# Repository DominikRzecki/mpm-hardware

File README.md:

# mpm-hardware
Mobile power measurement. Hardware repo
Update

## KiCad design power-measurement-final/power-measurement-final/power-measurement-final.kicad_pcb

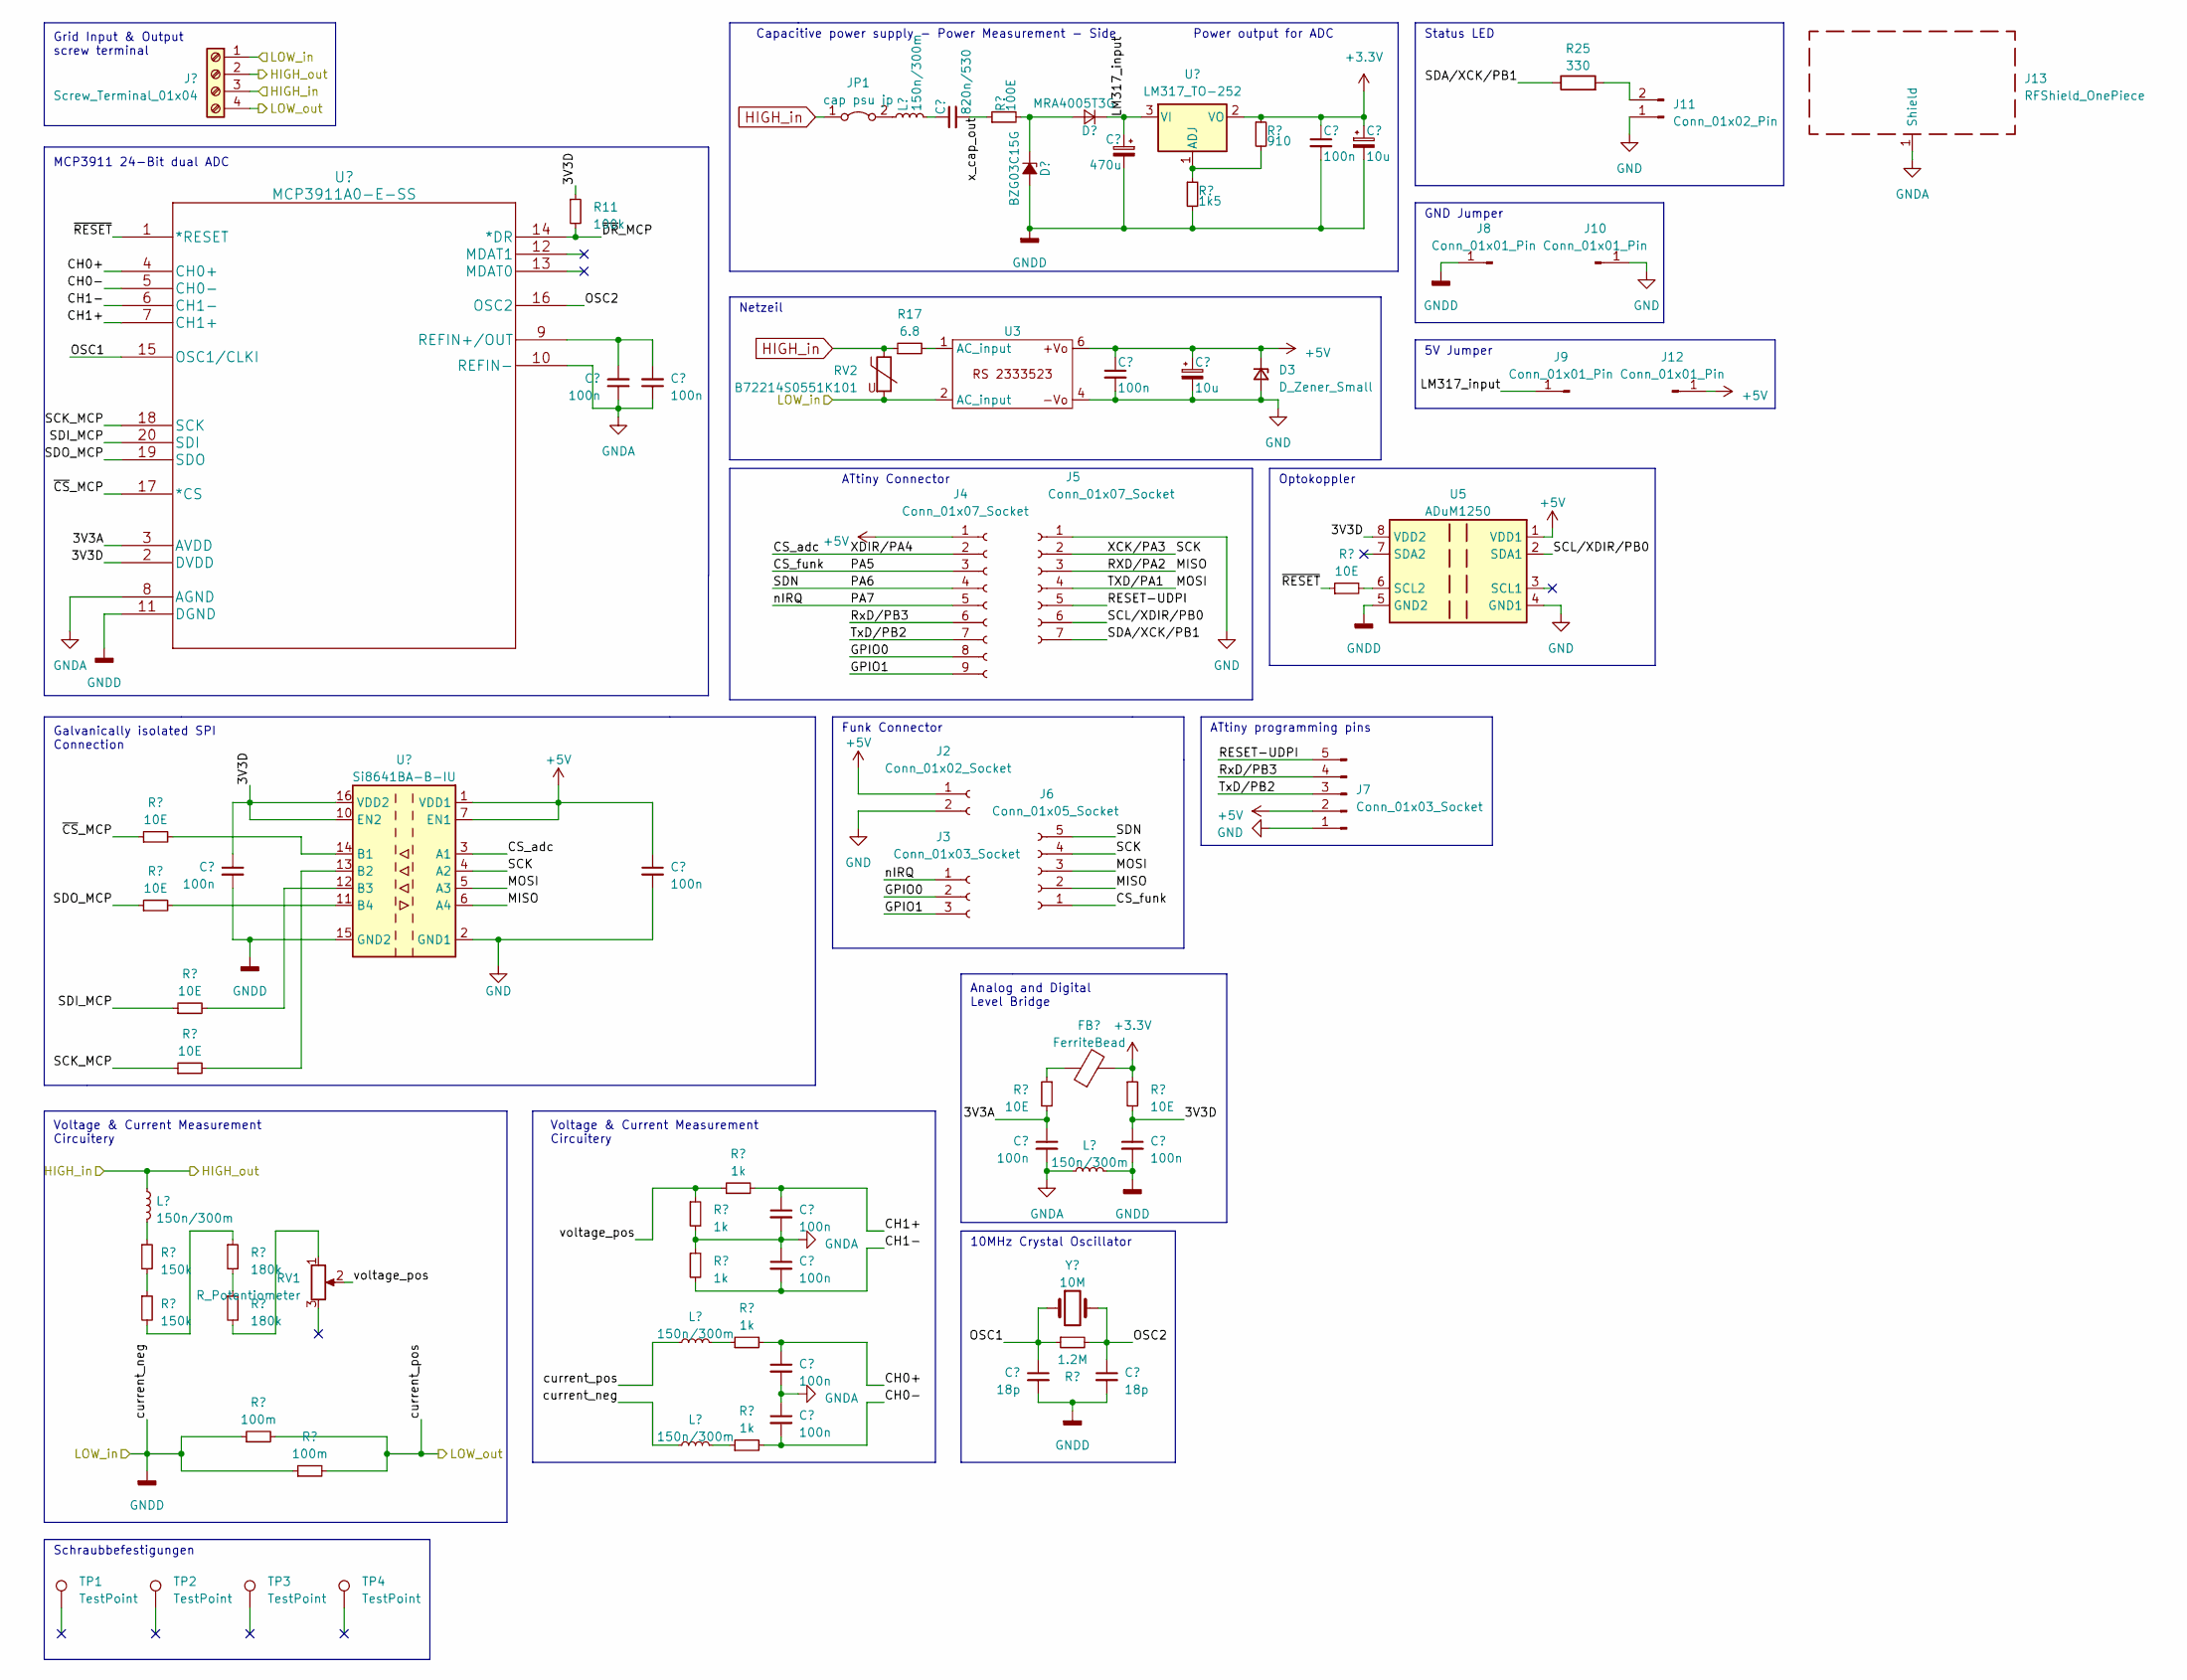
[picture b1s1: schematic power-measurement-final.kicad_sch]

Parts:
C1, C2, C3, C4, C5, C6, C7, C8, C11, C13, C15, C17: 100n; C_1206_3216Metric_Pad1.33x1.80mm_HandSolder
C9: 820n/530; C_Rect_L26.5mm_W10.5mm_P22.50mm_MKS4
C10, C12: 18p; C_0805_2012Metric_Pad1.18x1.45mm_HandSolder
C14: 470u; CP_Radial_D10.0mm_P5.00mm
C16, C18: 10u; C_1206_3216Metric_Pad1.33x1.80mm_HandSolder
D1: BZG03C15G; D_SMA-SMB_Universal_Handsoldering
D2: MRA4005T3G; D_MicroMELF_Handsoldering
D3: D_Zener_Small; D_1206_3216Metric_Pad1.42x1.75mm_HandSolder
FB1: FerriteBead; L_1210_3225Metric_Pad1.42x2.65mm_HandSolder
J1: Screw_Terminal_01x04; PhoenixContact_MSTBVA_2,5_4-G-5,08_1x04_P5.08mm_Vertical
J2: Conn_01x02_Socket; PinSocket_1x02_P2.54mm_Vertical
J3: Conn_01x03_Socket; PinSocket_1x03_P2.54mm_Vertical
J4: Conn_01x07_Socket; PinSocket_1x09_P2.54mm_Vertical
J5: Conn_01x07_Socket; PinSocket_1x07_P2.54mm_Vertical
J6: Conn_01x05_Socket; PinSocket_1x05_P2.54mm_Vertical
J7: Conn_01x03_Socket; PinHeader_1x05_P2.54mm_Vertical
J8, J9, J10, J12: Conn_01x01_Pin; PinHeader_1x01_P2.54mm_Vertical
J11: Conn_01x02_Pin; PinHeader_1x02_P2.54mm_Vertical
J13: RFShield_OnePiece; Laird_Technologies_BMI-S-209-F_29.36x18.50mm
JP1: cap psu jp; PinHeader_1x02_P2.54mm_Vertical
L1, L2, L3, L4, L5: 150n/300m; L_1206_3216Metric
R1, R2: 150k; R_1206_3216Metric_Pad1.30x1.75mm_HandSolder
R3, R4, R5, R6, R19, R21, R24: 10E; R_0805_2012Metric_Pad1.20x1.40mm_HandSolder
R7, R8: 180k; R_1206_3216Metric_Pad1.30x1.75mm_HandSolder
R9, R10: 100m; R_2512_6332Metric
R11: 100k; R_1206_3216Metric
R12, R13, R14, R15, R16: 1k; R_1206_3216Metric_Pad1.30x1.75mm_HandSolder
R17: 6.8; R_Radial_Power_L12.0mm_W8.0mm_P5.00mm
R18: 100E; R_1206_3216Metric_Pad1.30x1.75mm_HandSolder
R20: 1.2M; R_1206_3216Metric_Pad1.30x1.75mm_HandSolder
R22: 1k5; R_1206_3216Metric_Pad1.30x1.75mm_HandSolder
R23: 910; R_1206_3216Metric_Pad1.30x1.75mm_HandSolder
R25: 330; R_1206_3216Metric_Pad1.30x1.75mm_HandSolder
RV1: R_Potentiometer; Potentiometer_ACP_CA9-V10_Vertical_Hole
RV2: B72214S0551K101; R_Axial_DIN0204_L3.6mm_D1.6mm_P7.62mm_Horizontal
TP1, TP2, TP3, TP4: TestPoint; TestPoint_Plated_Hole_D3.0mm
U1: MCP3911A0-E-SS; SSOP-20_5.3x7.2mm_P0.65mm
U2: Si8641BA-B-IU; SOIC-16_3.9x9.9mm_P1.27mm
U3: RS_2333523
U4: LM317_TO-252; TO-252-2
U5: ADuM1250; SO-8_5.3x6.2mm_P1.27mm
Y1: 10M; Crystal_HC49-4H_Vertical

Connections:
+3.3V: C17.1, C18.1, FB1.2, R21.1, R23.1, U4.2 (VO)
+5V: C4.1, C13.1, C16.1, D3.1 (K), J2.1, J4.1, J7.2, J12.1, U2.1 (VDD1), U2.7 (EN1), U3.6, U5.1 (VDD1)
/3V3A: C11.1, R19.2, U1.3 (AVDD)
/3V3D: C1.1, C15.1, R11.1, R21.2, U1.2 (DVDD), U2.10 (EN2), U2.16 (VDD2), U5.8 (VDD2)
/CH0+: C7.1, R15.2, U1.4 (CH0+)
/CH0-: C8.2, R16.2, U1.5 (CH0-)
/CH1+: C5.1, R14.2, U1.7 (CH1+)
/CH1-: C6.2, R13.2, U1.6 (CH1-)
/CS_adc: J4.2, U2.3 (A1)
/CS_funk: J4.3, J6.1
/GPIO0: J3.2, J4.8
/GPIO1: J3.3, J4.9
/LM317_input: C14.1, D2.1 (K), J9.1, U4.3 (VI)
/MISO: J5.3, J6.2, U2.6 (A4)
/MOSI: J5.4, J6.3, U2.5 (A3)
/OSC1: C10.1, R20.1, U1.15 (OSC1/CLKI), Y1.1
/OSC2: C12.1, R20.2, U1.16 (OSC2), Y1.2
/PA6: J4.4, J6.5
/PA7: J3.1, J4.5
/RESET-UDPI: J5.5, J7.5
/RxD/PB3: J4.6, J7.4
/SCK: J5.2, J6.4, U2.4 (A2)
/SCK_MCP: R6.1, U1.18 (SCK)
/SCL/XDIR/PB0: J5.6, U5.2 (SDA1)
/SDA/XCK/PB1: J5.7, R25.1
/SDI_MCP: R5.1, U1.20 (SDI)
/SDO_MCP: R4.1, U1.19 (SDO)
/TxD/PB2: J4.7, J7.3
/current_pos: J1.4, L2.1, R9.2, R10.2
/voltage_pos: R12.1, R14.1, RV1.2
/x_cap_out: C9.2, R18.1
/~CS_MCP: R3.1, U1.17 (*CS)
/~DR_MCP: R11.2, U1.14 (*DR)
/~RESET: R24.1, U1.1 (*RESET)
GND: C4.2, C13.2, C16.2, D3.2 (A), J2.2, J5.1, J7.1, J10.1, J11.1, U2.2 (GND1), U2.8 (GND1), U3.4, U5.4 (GND1)
GNDA: C2.1, C3.1, C5.2, C6.1, C7.2, C8.1, C11.2, J13.1 (Shield), L5.1, R12.2, R13.1, U1.8 (AGND), U1.10 (REFIN-)
GNDD: C1.2, C10.2, C12.2, C14.2, C15.2, C17.2, C18.2, D1.2 (A), J1.1, J8.1, L3.1, L5.2, R9.1, R10.1, R22.2, RV2.2, U1.11 (DGND), U2.9 (GND2), U2.15 (GND2), U3.2 (AC_input), U5.5 (GND2)
HIGH_in: J1.2, J1.3, JP1.1 (A), L1.1, R17.1, RV2.1
unnamed: C9.1, L4.2
unnamed: D1.1 (K), D2.2 (A), R18.2
unnamed: FB1.1, R19.1
unnamed: J11.2, R25.2
unnamed: JP1.2 (B), L4.1
unnamed: L1.2, R1.1
unnamed: L2.2, R15.1
unnamed: L3.2, R16.1
unnamed: R1.2, R2.1
unnamed: R2.2, R7.1
unnamed: R7.2, R8.1
unnamed: R8.2, RV1.1
unnamed: R17.2, U3.1 (AC_input)
unnamed: C2.2, C3.2, U1.9 (REFIN+/OUT)
unnamed: R3.2, U2.14 (B1)
unnamed: R6.2, U2.13 (B2)
unnamed: R5.2, U2.12 (B3)
unnamed: R4.2, U2.11 (B4)
unnamed: R22.1, R23.2, U4.1 (ADJ)
unnamed: R24.2, U5.6 (SCL2)

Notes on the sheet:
Netzeil
Voltage & Current Measurement Circuitery
10MHz Crystal Oscillator
Funk Connector
Status LED
ATtiny Connector
Optokoppler
MCP3911 24-Bit dual ADC
5V Jumper
Capacitive power supply - Power Measurement - Side
Power output for ADC
ATtiny programming pins
Schraubbefestigungen
GND Jumper
Galvanically isolated SPI Connection
Grid Input & Output screw terminal
Analog and Digital Level Bridge

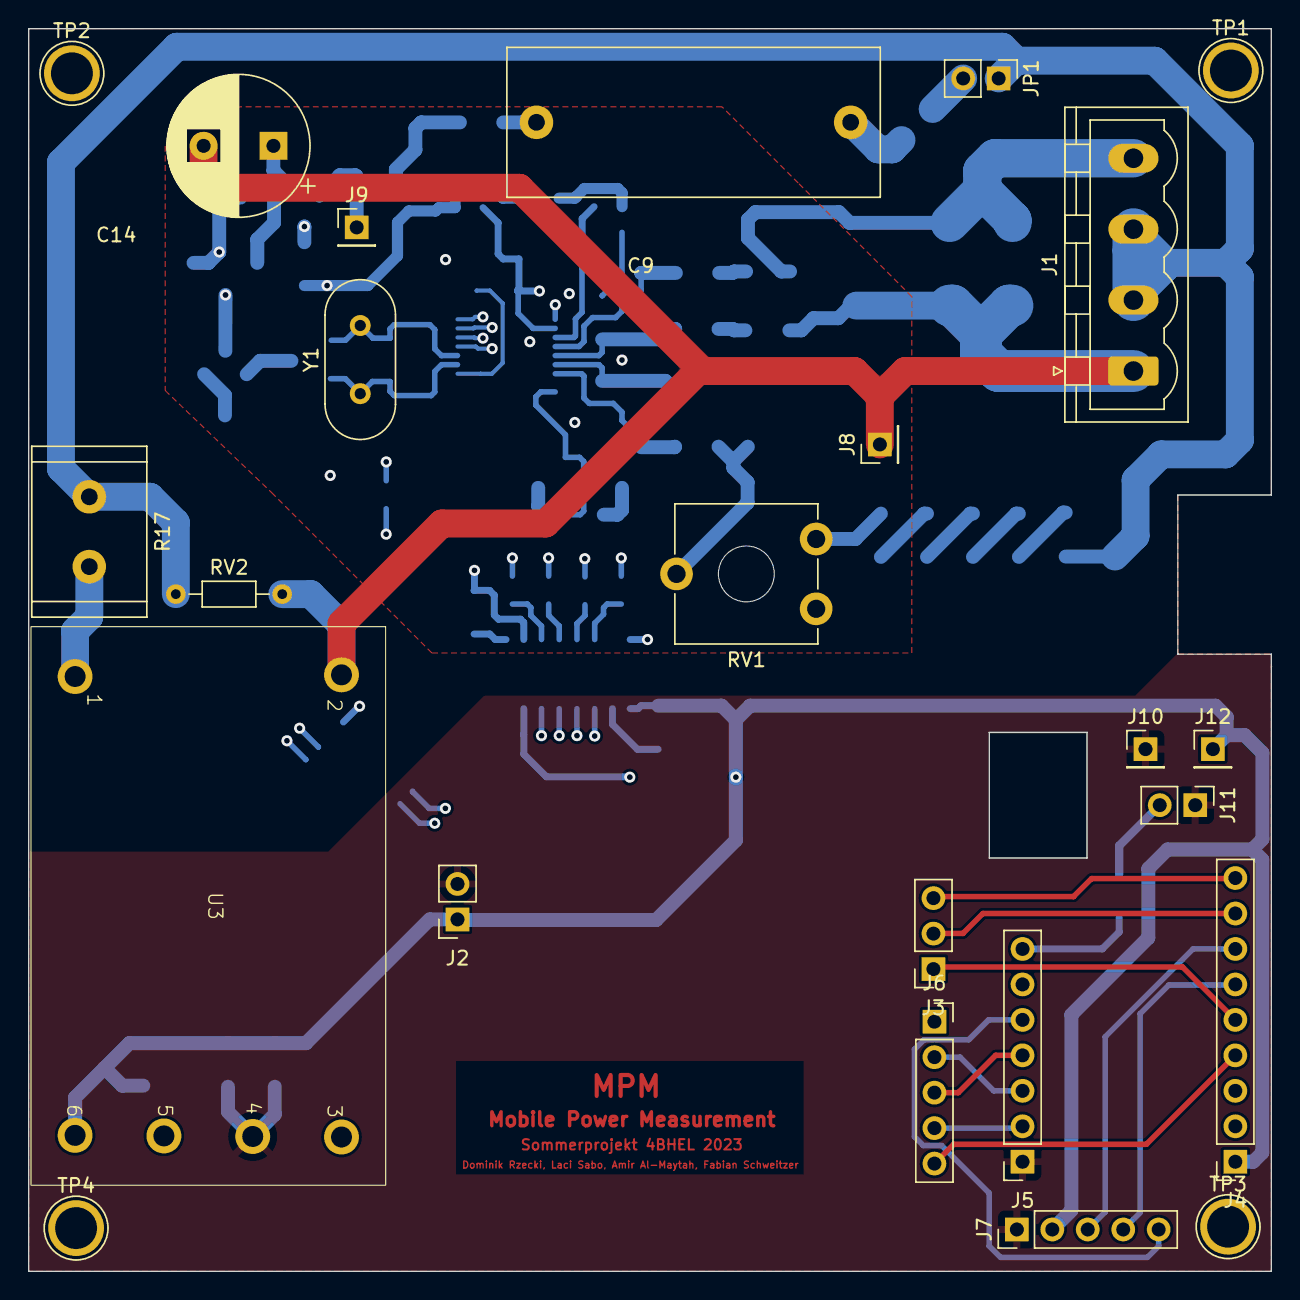
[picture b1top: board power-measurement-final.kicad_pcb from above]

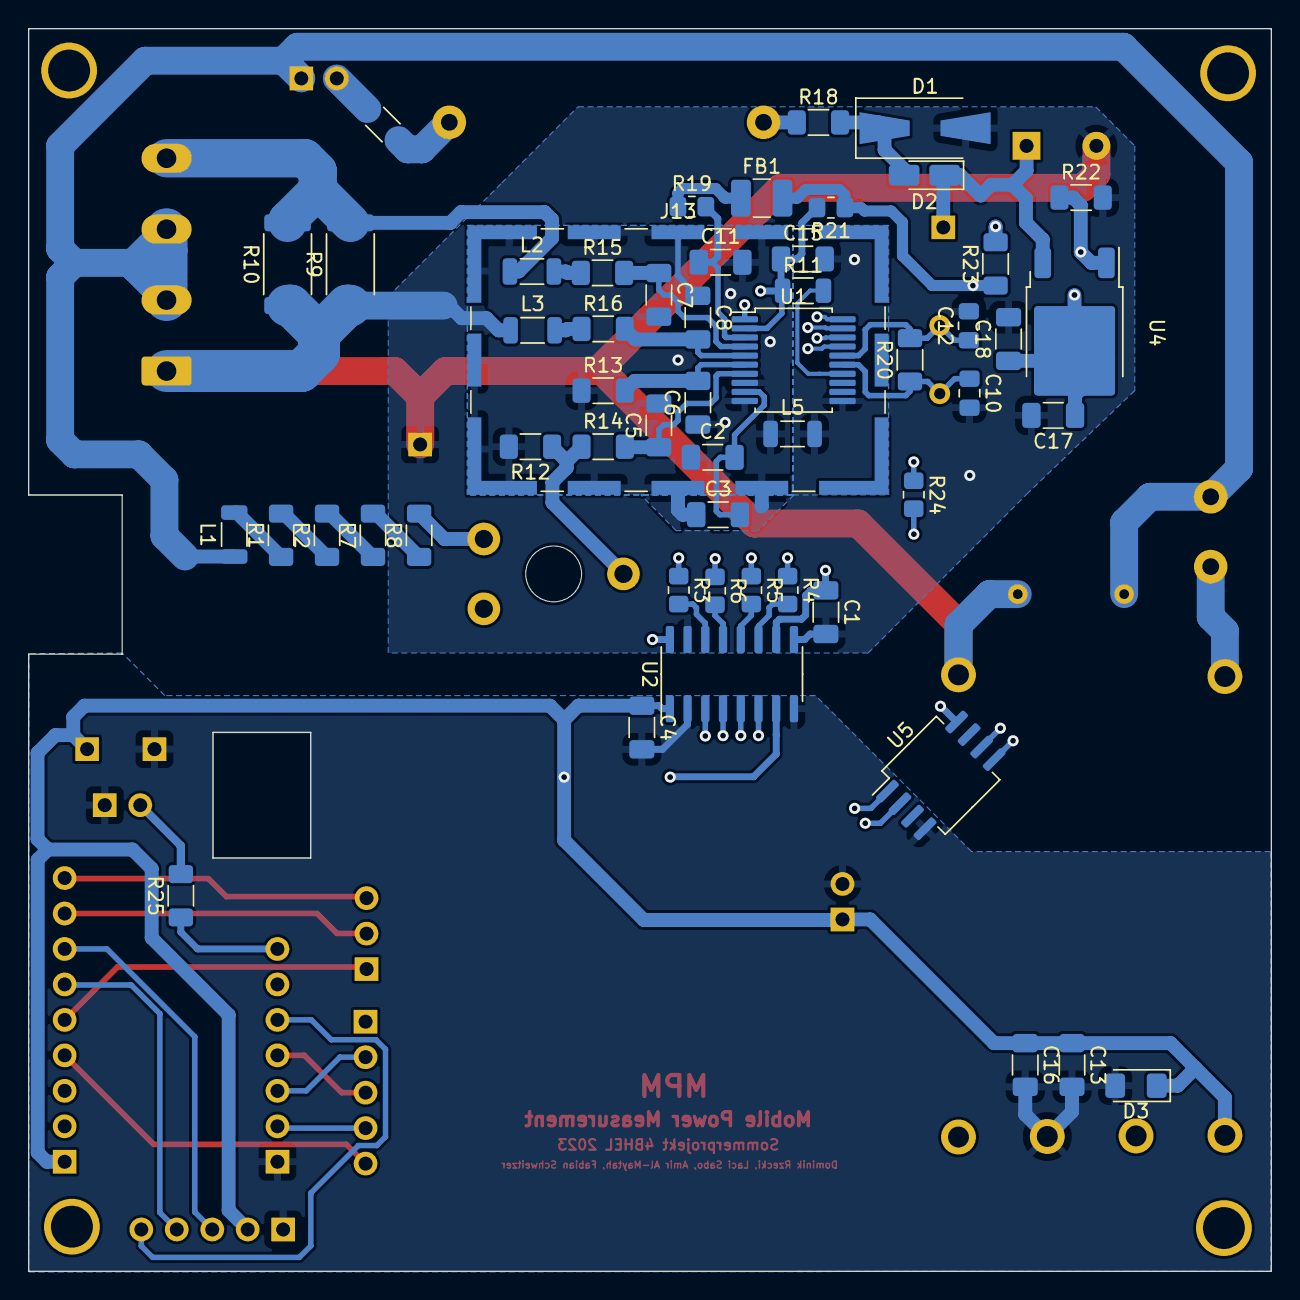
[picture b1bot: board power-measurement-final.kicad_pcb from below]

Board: 4 copper layers, 89.0 x 89.0 mm, 78 parts (54 on the bottom side), 58 nets.

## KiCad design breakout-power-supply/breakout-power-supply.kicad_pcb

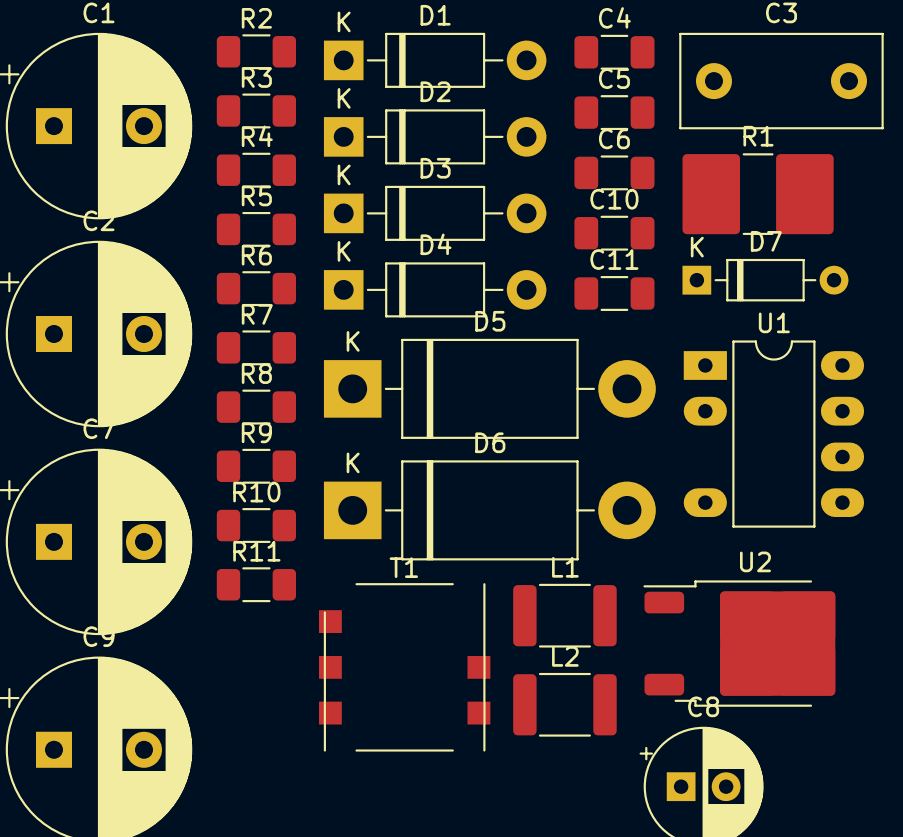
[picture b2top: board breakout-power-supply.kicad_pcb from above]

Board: 2 copper layers, 34 parts (0 on the bottom side), 20 nets, no tracks yet.

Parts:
C1, C2: 6u8; CP_Radial_D10.0mm_P5.00mm
C3: 1n; C_Disc_D11.0mm_W5.0mm_P7.50mm
C4, C5, C6: 1u; C_1206_3216Metric_Pad1.33x1.80mm_HandSolder
C7: 1000u; CP_Radial_D10.0mm_P5.00mm
C8: 470u; CP_Radial_D6.3mm_P2.50mm
C9: 470u; CP_Radial_D10.0mm_P5.00mm
C10: 100n; C_1206_3216Metric_Pad1.33x1.80mm_HandSolder
C11: 10u; C_1206_3216Metric_Pad1.33x1.80mm_HandSolder
D1, D2, D3, D4: 1N4007; D_DO-41_SOD81_P10.16mm_Horizontal
D5: D; D_DO-201AD_P15.24mm_Horizontal
D6: 1N5822; D_DO-201AD_P15.24mm_Horizontal
D7: 1N4148; D_DO-35_SOD27_P7.62mm_Horizontal
L1, L2: 1m; L_1812_4532Metric_Pad1.30x3.40mm_HandSolder
R1: 10E; R_2816_7142Metric_Pad3.20x4.45mm_HandSolder
R2: 270k; R_1206_3216Metric_Pad1.30x1.75mm_HandSolder
R3: 330E; R_1206_3216Metric_Pad1.30x1.75mm_HandSolder
R4, R8: 28.7k; R_1206_3216Metric_Pad1.30x1.75mm_HandSolder
R5: 4.42k; R_1206_3216Metric_Pad1.30x1.75mm_HandSolder
R6, R7: 12E; R_1206_3216Metric_Pad1.30x1.75mm_HandSolder
R9: 820E; R_1206_3216Metric_Pad1.30x1.75mm_HandSolder
R10: 1k5; R_1206_3216Metric_Pad1.30x1.75mm_HandSolder
R11: 910; R_1206_3216Metric_Pad1.30x1.75mm_HandSolder
T1: PA0510NL; Pulse_PA2002NL-PA2008NL-PA2009NL
U1: LNK625PG; PowerIntegrations_PDIP-8C
U2: LM317_TO-252; TO-252-2

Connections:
+3.3V: C10.1, C11.1, R11.1, U2.2 (VO)
/5V: C8.1, C9.1, L2.2, R9.2, U2.3 (VI)
/HIGH_in: D1.2 (A), D2.1 (K)
GND: C5.2, C7.2, C8.2, C9.2, C10.2, C11.2, D6.2 (A), R9.1, R10.2
unnamed: C2.2, C4.2, C6.2, L1.2, R5.1, T1.5, U1.5 (S), U1.6 (S), U1.7 (S), U1.8 (S)
unnamed: C3.2, R2.1, R3.2
unnamed: C5.1, R6.1
unnamed: C7.1, L2.1, T1.3
unnamed: C1.1, C2.1, C3.1, D1.1 (K), D3.1 (K), R2.2, T1.1
unnamed: C1.2, D2.2 (A), D4.2 (A), L1.1
unnamed: D3.2 (A), D4.1 (K), R1.2
unnamed: D5.2 (A), U1.4 (D)
unnamed: D5.1 (K), R3.1
unnamed: D6.1 (K), R6.2, T1.6
unnamed: D7.2 (A), R7.1
unnamed: C6.1, D7.1 (K), R8.2
unnamed: R4.2, R7.2, T1.4
unnamed: C4.1, R8.1, U1.2 (BP)
unnamed: R4.1, R5.2, U1.1 (FB)
unnamed: R10.1, R11.2, U2.1 (ADJ)

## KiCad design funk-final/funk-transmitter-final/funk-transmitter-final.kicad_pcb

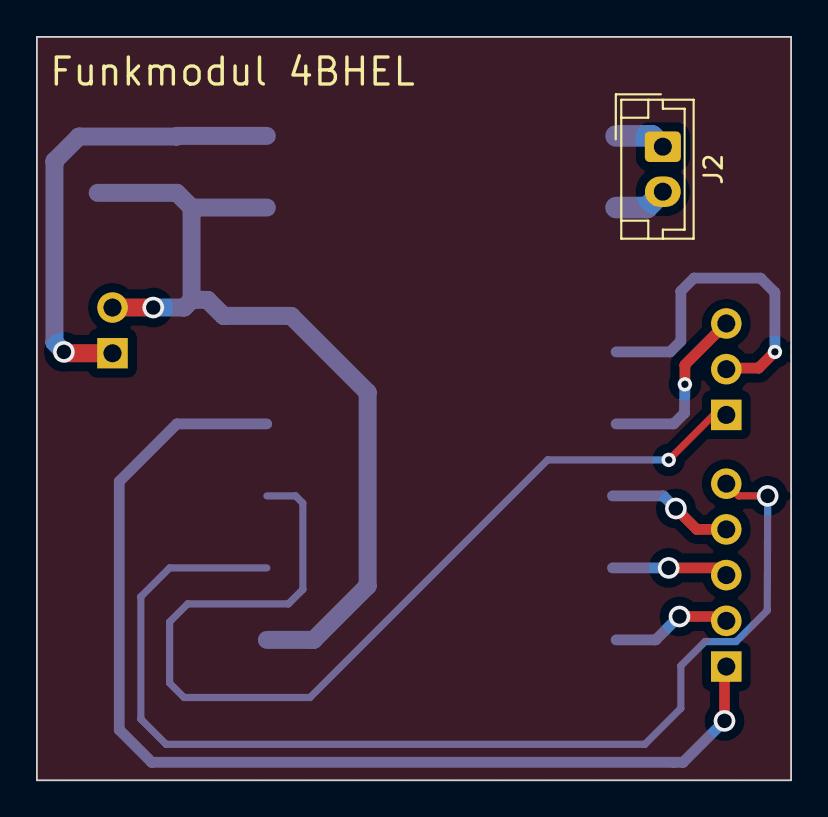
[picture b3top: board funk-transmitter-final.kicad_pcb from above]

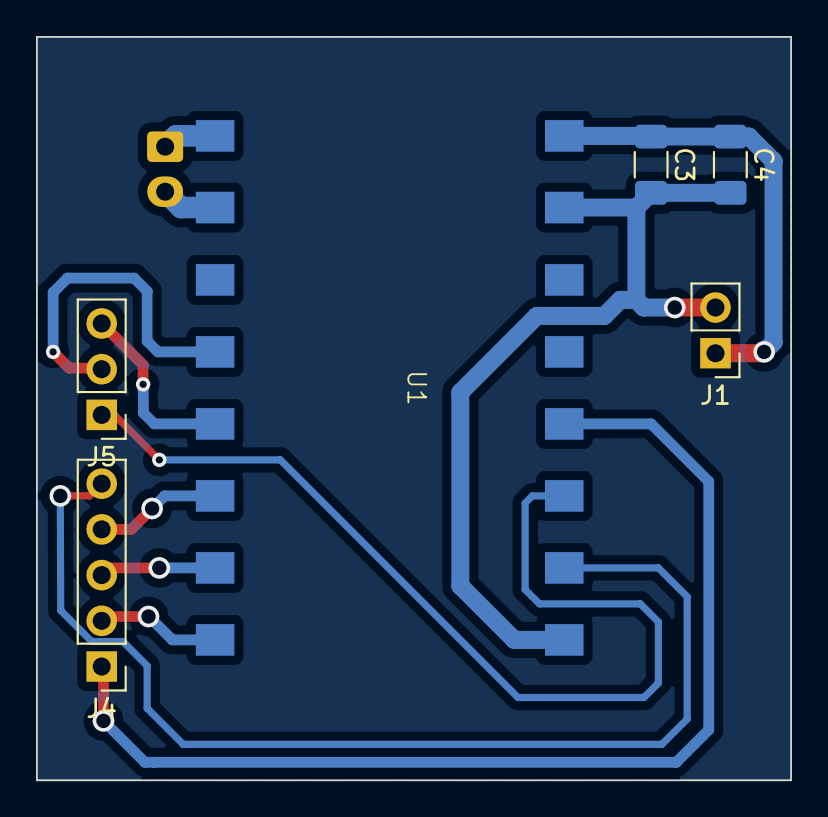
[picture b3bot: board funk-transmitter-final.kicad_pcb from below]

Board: 4 copper layers, 41.9 x 41.3 mm, 7 parts (6 on the bottom side), 9 nets.

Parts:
C3: 100n; C_1206_3216Metric_Pad1.33x1.80mm_HandSolder
C4: 47u; C_1206_3216Metric_Pad1.33x1.80mm_HandSolder
J1: Conn_01x02_Socket; PinHeader_1x02_P2.54mm_Vertical
J2: Conn_01x02_Socket; JST_EH_B2B-EH-A_1x02_P2.50mm_Vertical
J4: Conn_01x05_Socket; PinHeader_1x05_P2.54mm_Vertical
J5: Conn_01x03_Socket; PinHeader_1x03_P2.54mm_Vertical
U1: Si4463_eigen; Si4463

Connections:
/GPIO0: J5.2, U1.12 (GPIO0)
/GPIO1: J5.3, U1.13 (GPIO1)
/SCLK: J4.2, U1.16 (SCLK)
/SDI: J4.3, U1.15 (SDI)
/SDN: J4.1, U1.5 (SDN)
/SDO: J4.4, U1.14 (SDO)
/nIRQ: J5.1, U1.6 (nIRQ)
/nSEL: J4.5, U1.7 (nSEL)
GND: J1.2, U1.2 (GND), U1.8 (GND)

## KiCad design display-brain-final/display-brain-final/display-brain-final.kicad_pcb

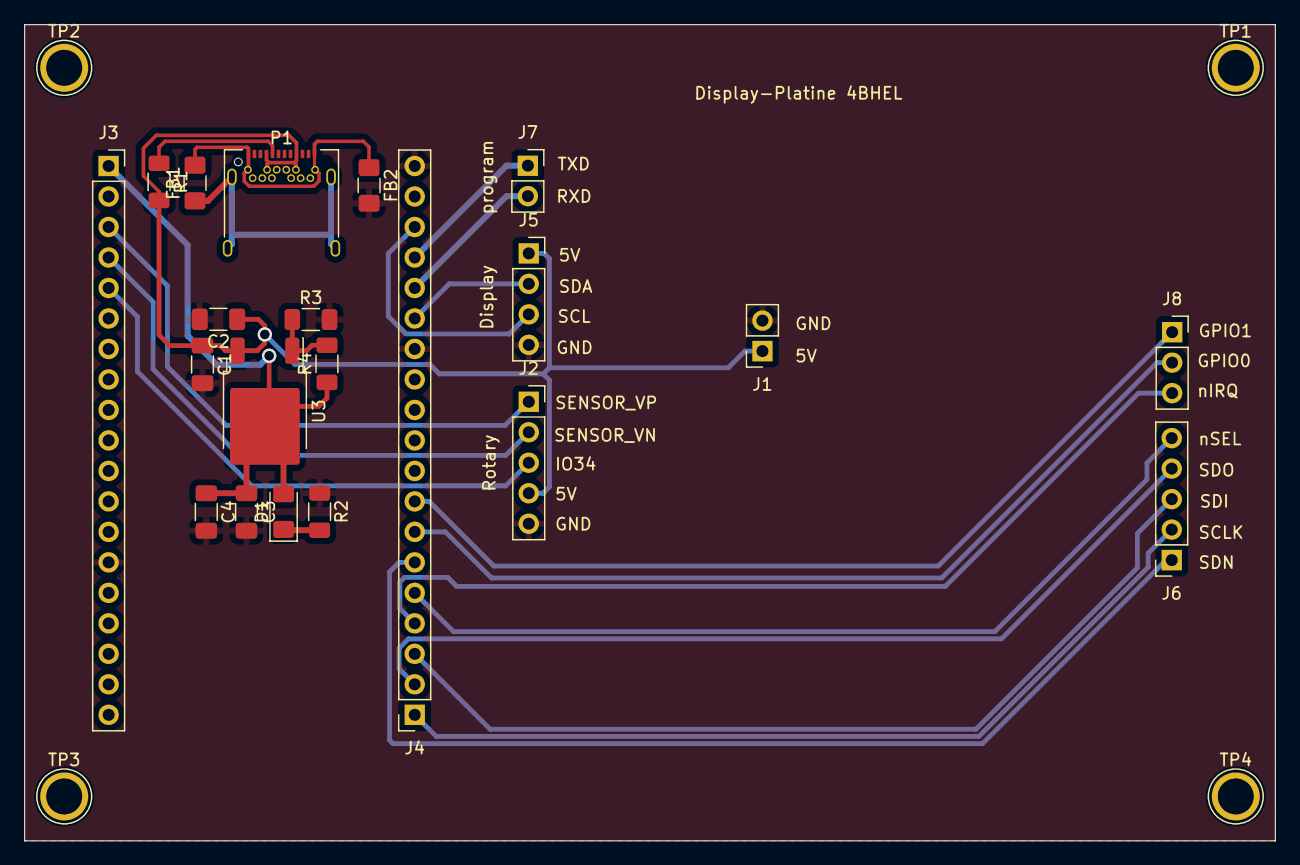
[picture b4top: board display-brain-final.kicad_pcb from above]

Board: 4 copper layers, 104.2 x 68.0 mm, 25 parts (0 on the bottom side), 23 nets.

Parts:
C1, C4: 10u; C_1206_3216Metric_Pad1.33x1.80mm_HandSolder
C2, C3: 100n; C_1206_3216Metric_Pad1.33x1.80mm_HandSolder
D1: LED; D_1206_3216Metric_Pad1.42x1.75mm_HandSolder
FB1, FB2: FerriteBead_Small; L_1206_3216Metric_Pad1.42x1.75mm_HandSolder
J1, J7: Conn_01x02_Socket; PinSocket_1x02_P2.54mm_Vertical
J2, J6: Conn_01x05_Socket; PinSocket_1x05_P2.54mm_Vertical
J3, J4: Conn_01x19_Socket; PinSocket_1x19_P2.54mm_Vertical
J5: Conn_01x04_Socket; PinSocket_1x04_P2.54mm_Vertical
J8: Conn_01x03_Socket; PinSocket_1x03_P2.54mm_Vertical
P1: USB_C_Plug_USB2.0; USB_C_Receptacle_Amphenol_12401548E4-2A
R1: 56k; R_1206_3216Metric_Pad1.30x1.75mm_HandSolder
R2: 330; R_1206_3216Metric_Pad1.30x1.75mm_HandSolder
R3: 1k5; R_1206_3216Metric_Pad1.30x1.75mm_HandSolder
R4: 910; R_1206_3216Metric_Pad1.30x1.75mm_HandSolder
TP1, TP2, TP3, TP4: TestPoint; TestPoint_Plated_Hole_D3.0mm
U3: LM317_TO-252; TO-252-2

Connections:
/3V3: C3.1, C4.1, D1.2 (A), J3.1, R4.1, U3.2 (VO)
/5V: C1.1, C2.1, J1.1, J2.4, J5.1, P1.A4 (VBUS), P1.A9 (VBUS), P1.B4 (VBUS), P1.B9 (VBUS), R1.2, U3.3 (VI)
/CLK: J4.1, J6.2
/IO0: J4.6, J6.1
/IO2: J4.5, J6.5
/IO4: J4.7, J8.2
/IO15: J4.4, J8.3
/IO16: J4.8, J8.1
/IO21_SDA: J4.14, J5.2
/IO22_SCL: J4.17, J5.3
/IO34: J2.3, J3.5
/RXD0: J4.15, J7.2
/SD0: J4.2, J6.4
/SD1: J4.3, J6.3
/SENSOR_VN: J2.2, J3.4
/SENSOR_VP: J2.1, J3.3
/TXD0: J4.16, J7.1
GND: C1.2, C2.2, C3.2, C4.2, FB2.2, J1.2, J2.5, J3.14, J4.13, J4.19, J5.4, R2.1, R3.2
unnamed: D1.1 (K), R2.2
unnamed: FB1.2, FB2.1, P1.A1 (GND), P1.A12 (GND), P1.B1 (GND), P1.B12 (GND)
unnamed: P1.A5 (CC), R1.1
unnamed: FB1.1, P1.S1 (SHIELD)
unnamed: R3.1, R4.2, U3.1 (ADJ)

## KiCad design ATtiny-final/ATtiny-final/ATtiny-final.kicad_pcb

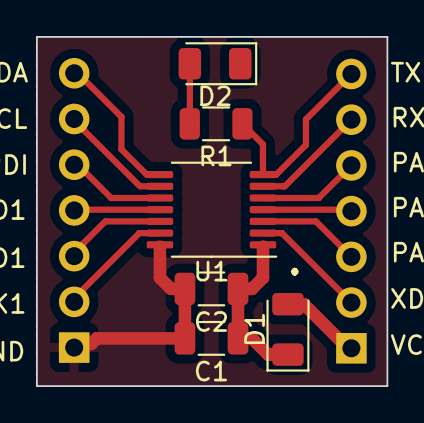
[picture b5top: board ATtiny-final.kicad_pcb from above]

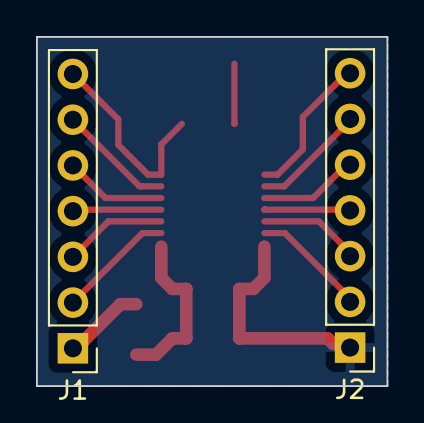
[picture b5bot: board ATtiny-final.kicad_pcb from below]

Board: 4 copper layers, 19.5 x 19.4 mm, 8 parts (2 on the bottom side), 2 nets.

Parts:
C1: 10n; C_1206_3216Metric
C2: 100n; C_1206_3216Metric
D1: D_Schottky; D_1206_3216Metric
D2: LED_Small; D_1206_3216Metric
J1, J2: Conn_01x07_Male; PinHeader_1x07_P2.54mm_Vertical
R1: 330; R_1206_3216Metric
U1: ATtiny424-X; TSSOP-14_4.4x5mm_P0.65mm

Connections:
/PA6: J1.4, U1.4 (PA6)
/XDIR/PA4: J1.2, U1.2 (PA4)

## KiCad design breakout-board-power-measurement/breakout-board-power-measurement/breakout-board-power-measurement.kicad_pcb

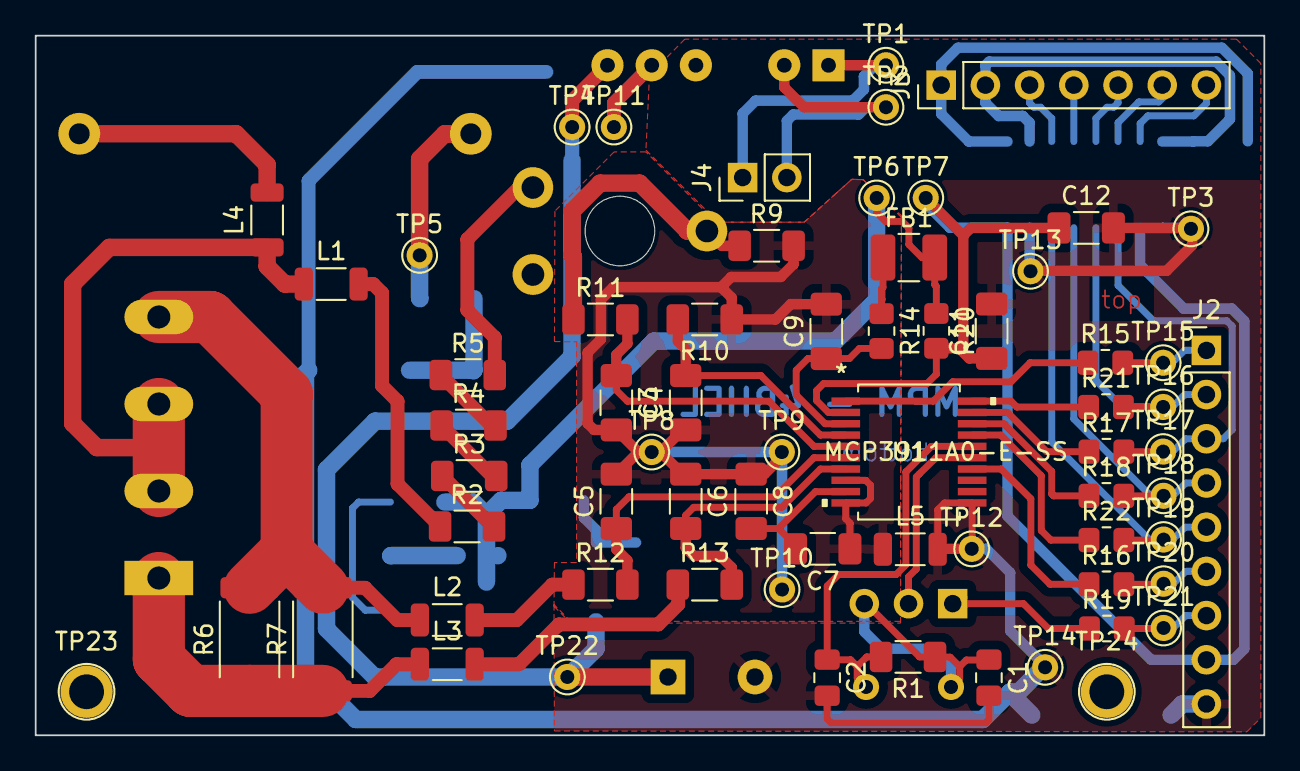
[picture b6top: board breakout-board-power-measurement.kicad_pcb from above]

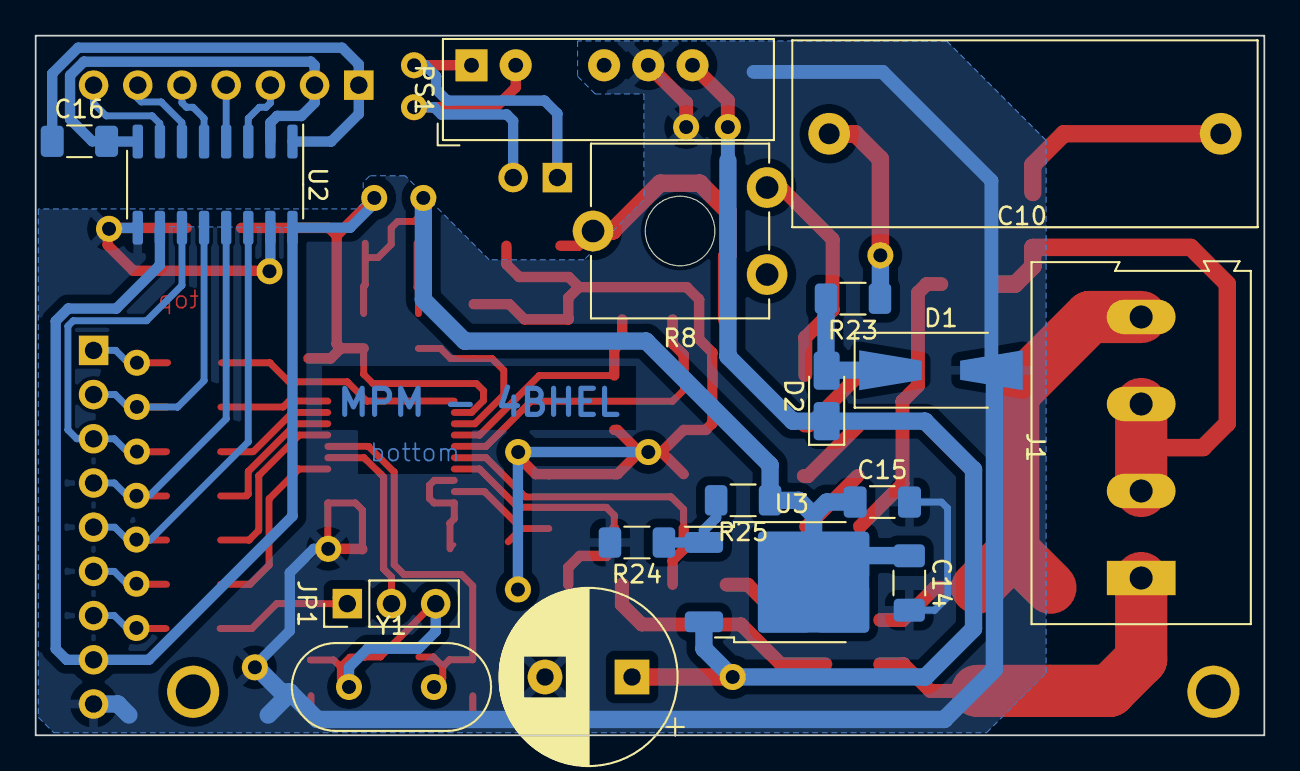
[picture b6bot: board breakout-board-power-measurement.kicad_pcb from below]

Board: 2 copper layers, 70.6 x 40.2 mm, 83 parts (17 on the bottom side), 53 nets.

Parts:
C1, C2: 18p; C_0805_2012Metric_Pad1.18x1.45mm_HandSolder
C3, C4, C5, C6, C7, C8, C9, C11, C12, C14, C16: 100n; C_1206_3216Metric_Pad1.33x1.80mm_HandSolder
C10: 820n/530; C_Rect_L26.5mm_W10.5mm_P22.50mm_MKS4
C13: 470u; CP_Radial_D10.0mm_P5.00mm
C15: 10u; C_1206_3216Metric_Pad1.33x1.80mm_HandSolder
D1: BZG03C15G; D_SMA-SMB_Universal_Handsoldering
D2: MRA4005T3G; D_MicroMELF_Handsoldering
FB1: FerriteBead; L_1210_3225Metric_Pad1.42x2.65mm_HandSolder
J1: Screw_Terminal_01x04; TerminalBlock_Altech_AK300-4_P5.00mm
J2: Conn_01x09; PinHeader_1x09_P2.54mm_Vertical
J3: Conn_01x07; PinHeader_1x07_P2.54mm_Vertical
J4: Conn_01x02; PinHeader_1x02_P2.54mm_Vertical
JP1: Jumper_3_Open; PinHeader_1x03_P2.54mm_Vertical
L1, L2, L3, L4, L5: 150n/300m; L_1206_3216Metric
PS1: IA0505S; Converter_DCDC_XP_POWER-IAxxxxS_THT
R1: 1.2M; R_1206_3216Metric_Pad1.30x1.75mm_HandSolder
R2, R3: 150k; R_1206_3216Metric_Pad1.30x1.75mm_HandSolder
R4, R5: 180k; R_1206_3216Metric_Pad1.30x1.75mm_HandSolder
R6, R7: 50m; R_2512_6332Metric
R8: 10k; Potentiometer_ACP_CA9-V10_Vertical_Hole
R9, R10, R11, R12, R13: 1k; R_1206_3216Metric_Pad1.30x1.75mm_HandSolder
R14, R15, R16, R17, R18, R19, R20, R21, R22: 10E; R_0805_2012Metric_Pad1.20x1.40mm_HandSolder
R23: 100E; R_1206_3216Metric_Pad1.30x1.75mm_HandSolder
R24: 1k5; R_1206_3216Metric_Pad1.30x1.75mm_HandSolder
R25: 910; R_1206_3216Metric_Pad1.30x1.75mm_HandSolder
TP1, TP2, TP3, TP4, TP5, TP6, TP7, TP8, TP9, TP10, TP11, TP12, TP13, TP14, TP15, TP16, TP17, TP18, TP19, TP20, TP21, TP22: TestPoint; Via_THTPad_D1.5mm_Drill0.8mm
TP23, TP24: TestPoint; Screwhole_THTPad_D3.0mm_Drill2.0mm
U1: MCP3911A0-E-SS; MCP3911A0-E&slash_SS
U2: Si8641BA-B-IU; SOIC-16_3.9x9.9mm_P1.27mm
U3: LM317_TO-252; TO-252-2
Y1: 10M; Crystal_HC49-4H_Vertical

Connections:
+3.3V: C14.1, C15.1, FB1.2, R20.1, R25.1, TP6.1, U3.2 (VO)
/3V3A: C9.1, R14.2, U1.3 (AVDD)
/3V3D: C11.1, C12.1, J2.8, R20.2, TP7.1, U1.2 (DVDD), U2.10 (EN2), U2.16 (VDD2)
/5V_ext: J4.1, PS1.1 (+Vin), TP1.1
/CH0+: C4.2, R10.2, U1.4 (CH0+)
/CH0-: C3.1, R11.2, U1.5 (CH0-)
/CH1+: C5.1, R12.2, U1.6 (CH1-)
/CH1-: C6.2, R13.2, U1.7 (CH1+)
/GND_ext: J4.2, PS1.2 (-Vin), TP2.1
/LM317_Vin: C13.1, D2.1 (K), PS1.6 (+Vout), TP4.1, TP22.1, U3.3 (VI)
/OSC1: C1.1, JP1.3 (B), R1.1, Y1.1
/OSC1_ext: JP1.1 (A), R19.1
/OSC1_ext_: J2.7, R19.2, TP21.1
/OSC2: C2.1, R1.2, U1.16 (OSC2), Y1.2
/SCK: R18.1, U1.18 (SCK)
/SCK_: J2.4, R18.2, TP18.1, U2.13 (B2)
/SDI: R21.1, U1.20 (SDI)
/SDI_: J2.2, R21.2, TP16.1, U2.12 (B3)
/SDO: R17.1, U1.19 (SDO)
/SDO_: J2.3, R17.2, TP17.1, U2.11 (B4)
/current_neg: J1.1, L3.1, R6.1, R7.1
/current_pos: J1.4, L2.1, R6.2, R7.2
/voltage_pos: R8.2, R9.1, R11.1
/x_cap_out: C10.2, R23.1, TP5.1
/~CS: R22.1, U1.17 (*CS)
/~CS_: J2.5, R22.2, TP19.1, U2.14 (B1)
/~DR: R16.1, U1.14 (*DR)
/~DR_: J2.6, R16.2, TP20.1
/~RESET: R15.1, U1.1 (*RESET)
/~RESET_: J2.1, R15.2, TP15.1
GNDA: C3.2, C4.1, C5.2, C6.1, C7.1, C8.1, C9.2, L5.1, R9.2, R10.1, TP8.1, TP9.1, TP10.1, U1.8 (AGND), U1.10 (REFIN-)
GNDD: C1.2, C2.2, C11.2, C12.2, C13.2, C14.2, C15.2, D1.2 (A), J2.9, L5.2, PS1.5 (0V), R24.2, TP3.1, TP11.1, TP12.1, TP13.1, TP14.1, U1.11 (DGND), U2.9 (GND2), U2.15 (GND2)
HIGH_in: J1.2, J1.3, L1.1, L4.1
unnamed: C10.1, L4.2
unnamed: D1.1 (K), D2.2 (A), R23.2
unnamed: FB1.1, R14.1
unnamed: C16.1, J3.1, U2.1 (VDD1)
unnamed: C16.2, J3.2, U2.2 (GND1), U2.8 (GND1)
unnamed: J3.3, U2.3 (A1)
unnamed: J3.4, U2.4 (A2)
unnamed: J3.5, U2.5 (A3)
unnamed: J3.6, U2.6 (A4)
unnamed: J3.7, U2.7 (EN1)
unnamed: JP1.2 (C), U1.15 (OSC1/CLKI)
unnamed: L1.2, R2.1
unnamed: L2.2, R12.1
unnamed: L3.2, R13.1
unnamed: R2.2, R3.1
unnamed: R3.2, R4.1
unnamed: R4.2, R5.1
unnamed: R5.2, R8.1
unnamed: C7.2, C8.2, U1.9 (REFIN+/OUT)
unnamed: R24.1, R25.2, U3.1 (ADJ)

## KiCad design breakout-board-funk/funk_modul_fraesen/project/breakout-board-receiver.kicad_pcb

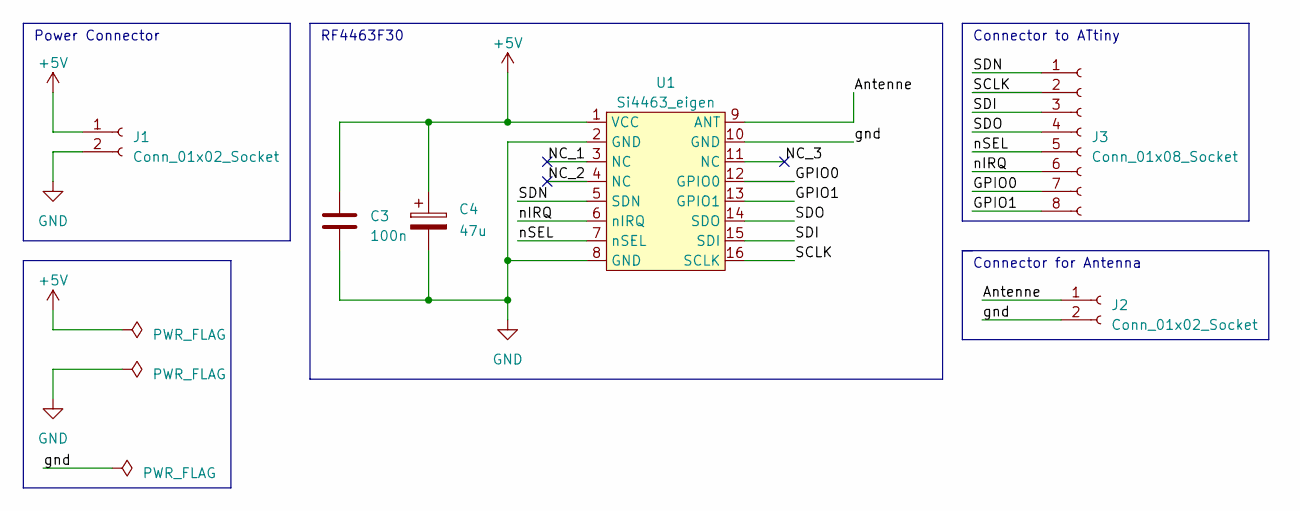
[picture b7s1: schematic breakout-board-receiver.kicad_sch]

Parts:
C3: 100n; C_1206_3216Metric_Pad1.33x1.80mm_HandSolder
C4: 47u; C_1206_3216Metric_Pad1.33x1.80mm_HandSolder
J1: Conn_01x02_Socket; PinSocket_1x02_P2.54mm_Vertical
J2: Conn_01x02_Socket; JST_EH_B2B-EH-A_1x02_P2.50mm_Vertical
J3: Conn_01x08_Socket; PinSocket_1x08_P2.54mm_Vertical
U1: Si4463_eigen; Si4463

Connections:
+5V: C3.1, C4.1, J1.1, U1.1 (VCC)
/Antenne: J2.1, U1.9 (ANT)
/GPIO0: J3.7, U1.12 (GPIO0)
/GPIO1: J3.8, U1.13 (GPIO1)
/NC_1: U1.3 (NC)
/NC_2: U1.4 (NC)
/NC_3: U1.11 (NC)
/SCLK: J3.2, U1.16 (SCLK)
/SDI: J3.3, U1.15 (SDI)
/SDN: J3.1, U1.5 (SDN)
/SDO: J3.4, U1.14 (SDO)
/gnd: J2.2, U1.10 (GND)
/nIRQ: J3.6, U1.6 (nIRQ)
/nSEL: J3.5, U1.7 (nSEL)
GND: C3.2, C4.2, J1.2, U1.2 (GND), U1.8 (GND)

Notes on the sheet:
RF4463F30
Power Connector
Connector to ATtiny
Connector for Antenna

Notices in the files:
parts and their libraries:
Copyright 2021 Accelerated Designs. All rights reserved.
